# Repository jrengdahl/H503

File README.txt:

STM32H503RB test board and firmware

This project includes a small OSHPark board for the new H503
microcontroller from ST MIcro, and firmware to run on the board. The
firmware includes OpenMP support for this bare metal microcontroller.

THE CHIP

The STM32H503 is a low-end microcontroller by ST Microelectronics:
-- Cortex-M33 CPU
-- 250 MHz
-- 128K flash
-- 32K RAM
-- typical peripherals for a small micro, including USB Device.
-- ETM trace port

When this chip first became available in early March of 2023, it was in
stock at Mouser for $4.33, and I was able to obtain a few. As of March
2024 they are available in small quantities from Digikey, directly from
ST Micro, and some other suppliers. Try findchips.com to search for
availability. Often such chips are more easily available on a Nucleo
board (although the Nucleo boards do not have trace connectors).

The spec clock for the H503 is 250 Hz. It seems to run reliably up to
350 MHz, and sometimes 400 MHz, at room temperature, and not using all
the chip's features. YMMV.

THE FIRMWARE

The firmware build is managed by an STM32CubeIDE project. The skeleton
of the project was auto-generated from the H503.ioc file. My firmware is
a simple command line interpeter with the following commands:

-- dump memory
-- modify memory
-- fill memory
-- RAM test
-- input from a pin
-- output to a pin
-- calibrate the CPU clock (to make sure the crystal, PLL, and spin-delay loop are correct)
-- set the CPU clock to a given frequency
-- execute a single LDR to a given memory location
-- execute a single STR to a given memory location
-- print a summary of the flash and RAM
-- run a benchmark of the thread switcher
-- display the on-chip temperature sensor reading
-- dump the thread stacks
-- display the state of the free memory system
-- run various OpenMP tests
-- set the debug verbosity level
-- print the help

The command line processor is simple and easily expanded with new commands.

The firmware takes about 40K of flash and 24K of RAM.

For similar L412 and H743 projects, rather than using an FTDI
USB-to-serial cable, or an on-board USB-to-serial chip, I decided to
learn how to use the native on-chip USB for the serial console. I got a
lot of help from Jean Roch's tutorial on using the STM32 USB CDC
library:
https://nefastor.com/microcontrollers/stm32/usb/stm32cube-usb-device-library

When I went to port this firmware over to the H503 I found that, since
the chip is very new, the USB_Device library is not yet available. With
some help from ST tech support, I was able to borrow code from similar
chips (the H743 and L552), and adapt it to the H503.

THREADS

I usually write bare metal firmware, with no OS or RTOS, but I use a
simple non-preemptive threading system, which enables me to architect a
system as a set of cooperating processes. As the concept developed over
many years it has gone by the name of "wait-wake", "plastic fork", and
"not-an-OS", but currently goes by the name of "Bear Metal Threads". Its
characteristics include:

-- very small: the code that gets used at runtime consists of 23 ASM
   instructions. There is a little more for creating threads at powerup. 
-- very fast: a thread switch takes 125 nanoseconds on a 250 MHz M33.
-- non-preemptive: there is no scheduler.
-- threads can run at interrupt level, which can provide prioritization.

OPENMP

One reason I created this project is as a platform to experiment with
bare metal OpenMP. 

OpenMP is a parallel processing extension for C/C++ and Fortran that is
built into GCC. It can be used on modern multi-core PCs running Windows
and Linux. It is most commonly associated with massively parallel
supercomputers such as Frontier and Fugaku (https://www.top500.org). I
aim to show that it can also be useful for multi-threaded and parallel
programming on single and multi-core embedded processors.

The following OpenMP features are working:
-- parallel
-- parallel for
-- single
-- task
-- firstprivate

I have started migrating the powerup code and command line interpreter
to using OpenMP primitives rather than the older threading calls to
spawn new threads.

This is experimental and ongoing.

THE GCC TOOLCHAIN

There are two reasons this firmware requires a special toolchain:

-- The threading system reserves r9 for the preempted thread stack. The
entire firmware must be compiled with the GCC flag "-ffixed-r9", so that
user code does not clobber r9. According to the AAPCS specification, r9
should be untouched by libraries. I have never seen a precompiled ibrary
that observes this rule. Fortunately, the ST-supplied code is always
compiled along with your firmware. Unfortunately, the precompiled newlib
that comes with the standard ARM bare metal GCC toolchain does not
follow the rule and clobbers r9.

-- GCC includes OpenMP, however it is only enabled for platforms that
have a large OS, such as Linux or Windows. The bare metal versions of
the toolchain do not have OpenMP enabled. My build of the GCC bare metal
toolchain has OpenMP enabled.

The Cortex-M33 GCC 12.2 toolchain to be used with this project is found at:
https://github.com/jrengdahl/cross/releases

THE BOARD

The KiCAD project for the board is included, or you can order three
boards from OSHPark for $16.
https://oshpark.com/shared_projects/t9n5Q26a

The board uses the Arduino Nano form factor, but is only partially
pin-compatible. It will fit into a Nano socket, such as this:
https://www.amazon.com/gp/product/B095XVVGQ8. Since the H503 is only
available in a 64-pin LQFP at the moment, in order to fit it on the
board I had to turn it 45 degrees, and delete the middle three pins from
each row of the connector. On the other hand, all pins on the
microcontroller either have a job, are brought out to pins, or are
brought out to solderable test points.

Interesting things about the board are:
-- Arduino Nano form factor
-- can be powered from the USB port
-- uses the on-chip USB for a virtual serial console
-- trace port
-- SPI flash

Otherwise the board is very minimal: power regulator, crystal
oscillator, connectors, a reset button, the BOOT0 button is also an GPIO
input, and one LED. I put a Winbond SPI flash on it because I want to
learn how to use them.

The microcontroller pinout is captured in a CubeMX project,
H503.kicad/H503.ioc. This is a sample CubeMX project I used as reference
for the board design, which shows a possible maximum usage of the pins.
The separate ./H503.ioc used by the firmware project only enables the
pins that are currently supported by the firmware.

Building the board is not hard. I do my soldering under a 1959
StereoZoom microscope using a very fine-tip pencil, and SMT solder paste
applied with a toothpick, or wire solder for through-hole parts. One
thing to watch out for is the USB connector. If you use too little
solder you risk ripping the connector off the board if you are not real
careful with the USB cable. If you use too much solder it can puddle
under the connector and short out the signal pins.

There is a newer version of the board that was manufactured by JLCPCB.
All the small commodity parts are located on the bottom side and are
soldered by JLCPCB. The CPU, connectors, and a couple parts that are
not sourced by JLCPCB are on the top side and have to be hand soldered.

The directory H503-0.1.oshpark contains the KiCad files that were used
for the OSHPark board. The directory H503-0.2.jlcpcb contains the KiCad
files for the JLCPCB board. The "production" subdirectory contains the
zip file that was uploaded to JLCPCB, including the BOM and
pick-and-place files. The directory H503-0.3 contains a slight
modification to the H503-0.2 board layout; mainly, the oscillator
footprint uses larger pads to make it easier to solder by hand. (I have
not had the 0.3 board built yet).

TRACE

One of my retirement presents to myself was a Segger J-Trace probe, so
I put a 20-pin trace port on this board rather than the usual four-pin
Serial Wire Debug port. If you don't have a trace probe you can populate
a 10-pin connector instead, and use a J-link or ST-Link probe. (You
can't fit a 10-pin connector onto a 20 pin header because the end of the
connector won't fit between the 5th and 6th pairs of pins).

One reason I prefer the M7 processors is that they include an on-chip
trace buffer, and a trace probe is not required. I use the free Segger
Ozone debugger, which can display trace for either on-chip or off-chip
trace. Unfortunately, since COVID, M7 chips are nearly impossible for a
hobbyist to obtain. That is why I have been focusing on the L412, and
more recently the H503. (Try lcsc.com if you need M7 chips, I found some
affordable H7B0).

In order to use ETM trace with Cortex-M4 and Cortex-M33 chips, the
following is required:

-- a chip that has trace port or on-chip trace buffer. As far as I know,
all STM32 in 100 pin packages or larger have trace ports. Trace ports on
smaller pinouts are less common. There is no easy way to find which chips
have trace capability, other than reading many data sheets. So far I
have found the STM32H503 and STM32L412 in LQFP-64, and the L412 in
LQFP-32, have 5-pin trace ports. In fact, the L412 seems to be the only
STM32 in LQFP-32 that has a trace port.

Some Cortex-M7 chips from ST Micro have 2K or 4K on-chip trace buffers.
These can be used with Ozone and an inexpensive J-Link Edu, though the
trace depth is limited.

-- a trace probe (unless you have an on-chip trace buffer). Trace probes
are expensive. I am familiar with Lauterbach, which costs in the
vicinity of $10,000. My Segger J-Trace was around $1800. In the UK or EU
check out pdqlogic.com, but they won't ship to the USA. Some people have
used inexpensive USB logic analyzers with the Sigrok software to capture
trace, but such a solution is harder to use
(https://essentialscrap.com/tips/arm_trace).

-- a trace capable debugger. I use Segger Ozone, which is included 
with J-Trace, or it is free for non-commercial use.

-- you have to allocate from two to five pins for the trace port. I have
always used the full five pins.

-- Your board has to have a trace port connector. The traces from the
chip to the connector should be laid out with high speed signalling in
mind. In theory, it might be possible to wire a trace probe to I/O pins
of a Nucleo board, but I would not expect this to work well at fast
clock rates. Though the H503 can run up to 250 MHz (400 MHz overclocked),
on my board the trace becomes flakey above 100 MHz.

-- You need to configure the trace pins. There are two ways to do this:

     -- your software can setup the pins and the ETM at powerup.
        Currently my L412 software does it this way. I based my ETM
        setup code on this project:
        https://github.com/PetteriAimonen/STM32_Trace_Example

     -- You can obtain or write an Ozone script to setup the trace
        pins. Once the pins are setup, Ozone can deal with the ETM and
        TPIU on its own. Segger provides compiled (.pex) scripts for
        certain chips. If your chip is not supported, or you have used a
        different pinout than Segger used, you either have to get them
        to create a .pex for you, or you can write your own script. This
        project includes a redistributable .jdebug script which sets up
        the pins for the H503.

   Having tried both methods, using the script works a lot better. Note
   that the H503 uses a different ETM than the L412. The L412 code will
   not work for the H503. It would be fairly difficult to research and
   write the ETM-M33 setup code, since you not only have to deal with
   the pins, but also the ETM and TPIU, for which I could find no
   easy-to-use documentation or example code. Also, when using the
   script, the trace starts at powerup, whereas if your software sets up
   the ETM, the trace only works after your code runs, and you have to
   stop and restart your program after the setup code before Ozone
   starts receiving trace data.

RTOS-AWARE TRACE

Segger's Ozone debugger can detect RTOS thread switches in order to make
the trace easier to read and understand. If you are using a supported
RTOS they have RTOS-awareness modules you can download and use. If your
RTOS is not supported, or home-brewed like mine, you can tell Ozone
about the thread switching code in the Ozone startup script. The .jdebug
script included with this project does that. There are two prequisites:
your thread switch code must exist in a subroutine call that Ozone can
find, and you have to use Dwarf-4 debug info. Newer editions of GCC,
such as 12.2, emit Dwarf-5 debug data by default, so you have to pass
-gdwarf-4 to the GCC and G++ compilers.

The newer version of Ozone supports Dwarf-5, but I have not tried
Dwarf-5 yet.

JLINK

There is an alternate H503-edu.jdebug file that works with a non-trace
Jlink. The J-link Edu comes with a 10-pin high density conector that
will work with this board if you install a 10 pin connector (or cut half
the pins from the 20-pin connector). Jlink EDU is $60 at
https://shop-us.segger.com/product/j-link-edu-mini-8-08-91 or
at Mouser or Digikey.

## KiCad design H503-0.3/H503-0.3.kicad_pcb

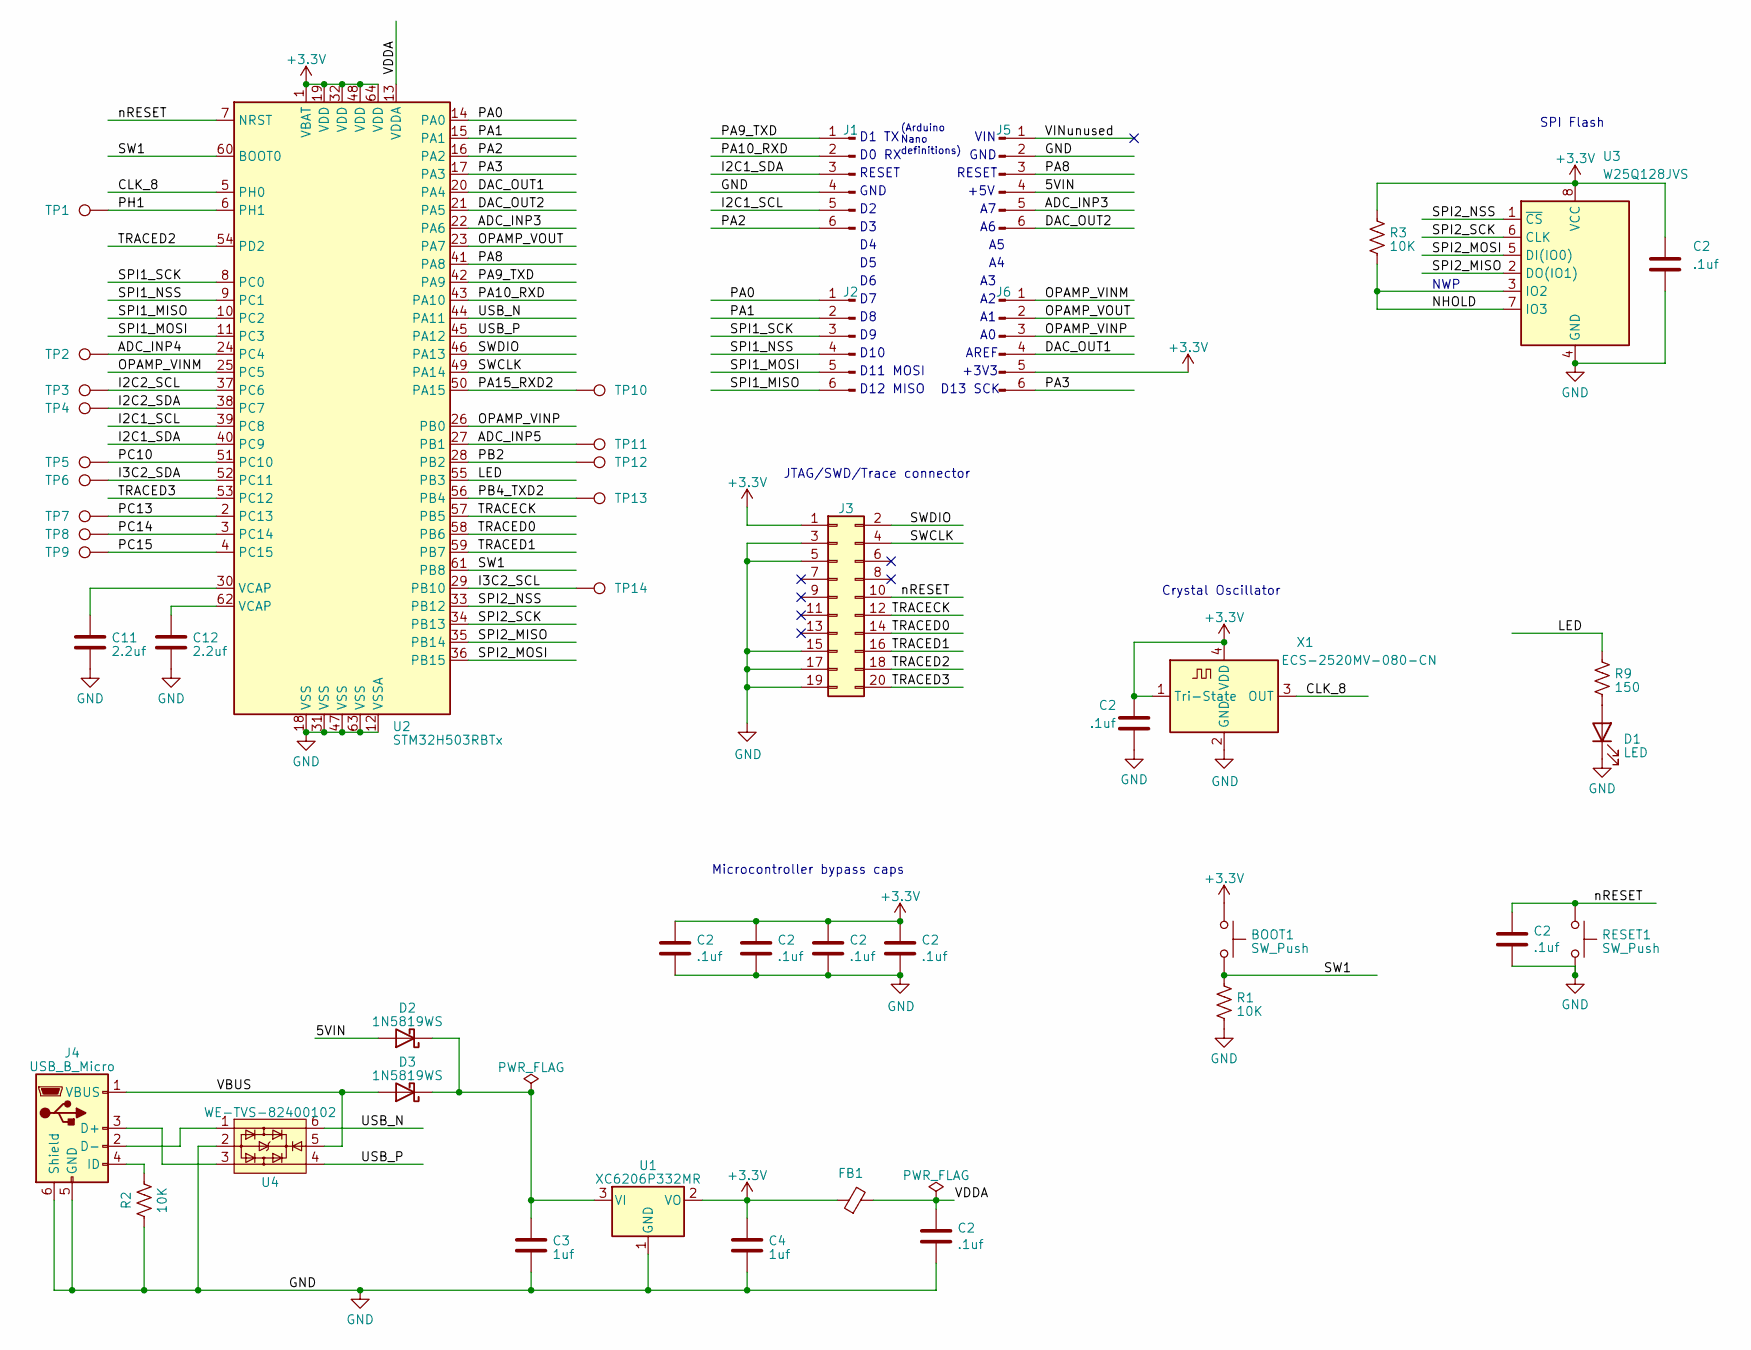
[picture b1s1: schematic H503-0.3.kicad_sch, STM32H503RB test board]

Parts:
BOOT1: SW_Push; SW_SPST_B3U-1000P
C2: .1uf; C_0603_1608Metric; LCSC C14663
C3, C4: 1uf; C_0805_2012Metric; LCSC C28323
C11, C12: 2.2uf; C_0805_2012Metric; LCSC C49217
D1: LED; LED_PLCC-2_3.4x3.0mm_KA
D2, D3: 1N5819WS; D_SOD-323; LCSC C191023
FB1: C_0603_1608Metric; LCSC C1002
J1, J2, J5, J6: Conn_01x06_Pin; PinHeader_1x06_P2.54mm_Vertical__min
J3: Conn_02x10_Odd_Even; PinHeader_2x10_P1.27mm_Vertical
J4: USB_B_Micro; USB_Micro-B_Amphenol_10118194_Horizontal
R1, R2, R3: 10K; R_0603_1608Metric; LCSC C25804
R9: 150; R_0603_1608Metric; LCSC C22808
RESET1: SW_Push; SW_SPST_B3U-1000P
TP1, TP2, TP3, TP4, TP5, TP6, TP7, TP8, TP9, TP10, TP11, TP12, TP13, TP14: TestPoint; TestPoint_THTPad_D1.0mm_Drill0.5mm_min
U1: XC6206P332MR; SOT-23-3; LCSC C5446
U2: STM32H503RBTx; LQFP-64_10x10mm_P0.5mm
U3: W25Q128JVS; SOIC-8_5.23x5.23mm_P1.27mm
U4: WE-TVS-82400102; SOT-23-6
X1: ECS-2520MV-080-CN; Oscillator_SMD_ECS_2520MV-4Pin_2.5x2.0mm-hand-solder

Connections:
/5VIN: D2.2 (A), J5.4
/ADC_INP3: J5.5, U2.22 (PA6)
/ADC_INP4: TP2.1, U2.24 (PC4)
/ADC_INP5: TP11.1, U2.27 (PB1)
/CLK_8: U2.5 (PH0), X1.3 (OUT)
/DAC_OUT1: J6.4, U2.20 (PA4)
/DAC_OUT2: J5.6, U2.21 (PA5)
/I2C1_SCL: J1.5, U2.39 (PC8)
/I2C1_SDA: J1.3, U2.40 (PC9)
/I2C2_SCL: TP3.1, U2.37 (PC6)
/I2C2_SDA: TP4.1, U2.38 (PC7)
/I3C2_SCL: TP14.1, U2.29 (PB10)
/I3C2_SDA: TP6.1, U2.52 (PC11)
/LED: R9.2, U2.55 (PB3)
/NHOLD: R3.2, U3.3 (IO2), U3.7 (IO3)
/OPAMP_VINM: J6.1, U2.25 (PC5)
/OPAMP_VINP: J6.3, U2.26 (PB0)
/OPAMP_VOUT: J6.2, U2.23 (PA7)
/PA0: J2.1, U2.14 (PA0)
/PA1: J2.2, U2.15 (PA1)
/PA2: J1.6, U2.16 (PA2)
/PA3: J6.6, U2.17 (PA3)
/PA8: J5.3, U2.41 (PA8)
/PA9_TXD: J1.1, U2.42 (PA9)
/PA10_RXD: J1.2, U2.43 (PA10)
/PA15_RXD2: TP10.1, U2.50 (PA15)
/PB2: TP12.1, U2.28 (PB2)
/PB4_TXD2: TP13.1, U2.56 (PB4)
/PC10: TP5.1, U2.51 (PC10)
/PC13: TP7.1, U2.2 (PC13)
/PC14: TP8.1, U2.3 (PC14)
/PC15: TP9.1, U2.4 (PC15)
/PH1: TP1.1, U2.6 (PH1)
/SPI1_MISO: J2.6, U2.10 (PC2)
/SPI1_MOSI: J2.5, U2.11 (PC3)
/SPI1_NSS: J2.4, U2.9 (PC1)
/SPI1_SCK: J2.3, U2.8 (PC0)
/SPI2_MISO: U2.35 (PB14), U3.2 (DO(IO1))
/SPI2_MOSI: U2.36 (PB15), U3.5 (DI(IO0))
/SPI2_NSS: U2.33 (PB12), U3.1 (~CS)
/SPI2_SCK: U2.34 (PB13), U3.6 (CLK)
/SW1: BOOT1.2, R1.1, U2.60 (BOOT0), U2.61 (PB8)
/SWCLK: J3.4, U2.49 (PA14)
/SWDIO: J3.2, U2.46 (PA13)
/TRACECK: J3.12, U2.57 (PB5)
/TRACED0: J3.14, U2.58 (PB6)
/TRACED1: J3.16, U2.59 (PB7)
/TRACED2: J3.18, U2.54 (PD2)
/TRACED3: J3.20, U2.53 (PC12)
/USB_N: U2.44 (PA11), U4.6
/USB_P: U2.45 (PA12), U4.4
/VBUS: D3.2 (A), J4.1 (VBUS), U4.5
/VINunused: J5.1
GND: C2.2, C3.2, C4.2, C11.2, C12.2, D1.1 (K), J1.4, J3.3, J3.5, J3.15, J3.17, J3.19, J4.5 (GND), J4.6 (Shield), J5.2, R1.2, R2.1, RESET1.2, U1.1 (GND), U2.12 (VSSA), U2.18 (VSS), U2.31 (VSS), U2.47 (VSS), U2.63 (VSS), U3.4 (GND), U4.2, X1.2 (GND); also elsewhere on the board
unnamed: C3.1, D2.1 (K), D3.1 (K), U1.3 (VI)
unnamed: C11.1, U2.30 (VCAP)
unnamed: C12.1, U2.62 (VCAP)
unnamed: D1.2 (A), R9.1
unnamed: J4.3 (D+), U4.3
unnamed: J4.2 (D-), U4.1
unnamed: J4.4 (ID), R2.2

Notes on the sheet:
+3V3
SPI Flash
VIN
NWP
+5V
GND
Microcontroller bypass caps
D13 SCK
D12 MISO
Crystal Oscillator
D1 TX
RESET
JTAG/SWD/Trace connector
D11 MOSI
D0 RX
(Arduino Nano definitions)
AREF
D10

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
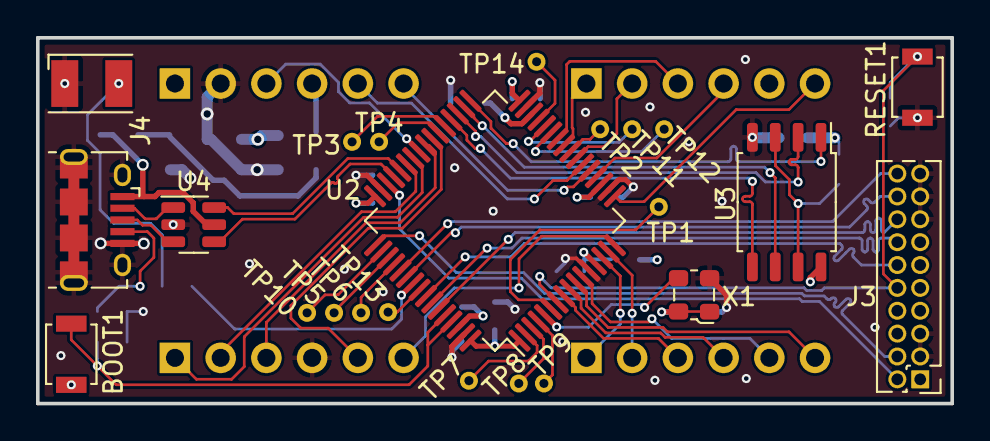
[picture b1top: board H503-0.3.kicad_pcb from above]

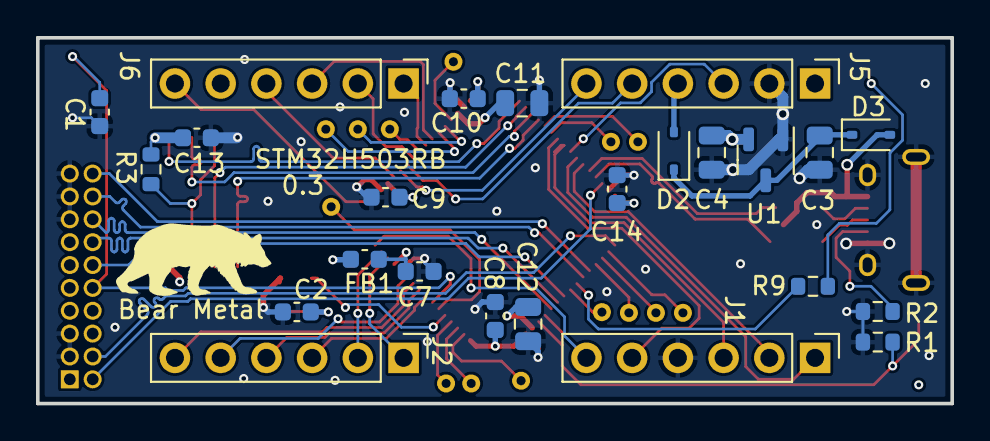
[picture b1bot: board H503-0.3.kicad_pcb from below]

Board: 4 copper layers, 50.8 x 20.3 mm, 47 parts (24 on the bottom side), 63 nets.

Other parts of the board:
C1, C7, C8, C9, C10, C13, C14: .1uf; C_0603_1608Metric

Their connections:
GND: C1.2, C7.2, C8.2, C9.2, C10.2, C13.2, C14.2; also elsewhere on the board

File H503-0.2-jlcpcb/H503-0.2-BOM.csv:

"Id";"Designator";"Footprint";"Quantity";"Designation";"Supplier and ref";
1;"X1";"Oscillator_SMD_ECS_2520MV-xxx-xx-4Pin_2.5x2.0mm";1;"ECS-2520MV-080-CN";;;
2;"TP1,TP3,TP7,TP14,TP9,TP6,TP11,TP5,TP8,TP12,TP4,TP13,TP2,TP10";"TestPoint_THTPad_D1.0mm_Drill0.5mm_min";14;"TestPoint";;;
3;"BOOT1,RESET1";"SW_SPST_B3U-1000P";2;"SW_Push";;;
4;"J3";"PinHeader_2x10_P1.27mm_Vertical";1;"Conn_02x10_Odd_Even";;;
5;"U4";"SOT-23-6";1;"WE-TVS-82400102";;;
6;"J4";"USB_Micro-B_Amphenol_10118194_Horizontal";1;"USB_B_Micro";;;
7;"U2";"LQFP-64_10x10mm_P0.5mm";1;"STM32H503RBTx";;;
8;"U3";"SOIC-8_5.23x5.23mm_P1.27mm";1;"W25Q128JVS";;;
9;"D1";"LED_PLCC-2_3.4x3.0mm_KA";1;"LED";;;
10;"C10,C14,C1,C9,C8,C7,C2,C13";"C_0603_1608Metric";8;".1uf";;;
11;"U1";"SOT-23-3";1;"XC6206P332MR";;;
12;"R1,R2,R3";"R_0603_1608Metric";3;"10K";;;
13;"J1,J2,J6,J5";"PinHeader_1x06_P2.54mm_Vertical__min";4;"Conn_01x06_Pin";;;
14;"FB1";"C_0603_1608Metric";1;"~";;;
15;"D2,D3";"D_SOD-323";2;"1N5819WS";;;
16;"C11,C12";"C_0805_2012Metric";2;"2.2uf";;;
17;"R9";"R_0603_1608Metric";1;"150";;;
18;"C3,C4";"C_0805_2012Metric";2;"1uf";;;

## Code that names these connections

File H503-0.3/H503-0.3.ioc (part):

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Mcu.Name=STM32H503RBTx
Mcu.Package=LQFP64
Mcu.UserName=STM32H503RBTx
PA0.Mode=NSS_Signal_Hard_Output
PA0.Signal=SPI3_NSS
PA1.Mode=Full_Duplex_Master
PA1.Signal=SPI3_SCK
PA10.Mode=Asynchronous
PA10.Signal=USART1_RX
PA11.Mode=Device
PA11.Signal=USB_DM
PA12.Mode=Device
PA12.Signal=USB_DP
PA13(JTMS/SWDIO).GPIOParameters=GPIO_Label
PA13(JTMS/SWDIO).GPIO_Label=SWDIO
PA13(JTMS/SWDIO).Mode=Trace_Synchro_4bits_SW
PA13(JTMS/SWDIO).Signal=DEBUG_JTMS-SWDIO
PA14(JTCK/SWCLK).GPIOParameters=GPIO_Label
PA14(JTCK/SWCLK).GPIO_Label=SWCLK
PA14(JTCK/SWCLK).Mode=Trace_Synchro_4bits_SW
PA14(JTCK/SWCLK).Signal=DEBUG_JTCK-SWCLK
PA15(JTDI).Mode=Asynchronous
PA15(JTDI).Signal=USART2_RX
PA2.Mode=Full_Duplex_Master
PA2.Signal=SPI3_MISO
PA3.Mode=Full_Duplex_Master
PA3.Signal=SPI3_MOSI
PA4.Signal=COMP_DAC11_group
PA5.Signal=COMP_DAC12_group
PA6.Signal=ADCx_INP3
PA7.Signal=SharedAnalog_PA7
PA8.GPIOParameters=GPIO_Label
PA8.GPIO_Label=PA8
PA8.Signal=GPIO_Input
PA9.Mode=Asynchronous
PA9.Signal=USART1_TX
PB0.Mode=Standalone
PB0.Signal=OPAMP1_VINP
PB1.Signal=ADCx_INP5
PB10.Mode=Controller
PB10.Signal=I3C2_SCL
PB12.Mode=NSS_Signal_Hard_Output
PB12.Signal=SPI2_NSS
PB13.Mode=Full_Duplex_Master
PB13.Signal=SPI2_SCK
PB14.Mode=Full_Duplex_Master
PB14.Signal=SPI2_MISO
PB15.Mode=Full_Duplex_Master
PB15.Signal=SPI2_MOSI
PB2.GPIOParameters=GPIO_Label
PB2.GPIO_Label=PB2
PB2.Signal=GPIO_Input
PB3(JTDO/TRACESWO).GPIOParameters=GPIO_Label
PB3(JTDO/TRACESWO).GPIO_Label=LED
PB3(JTDO/TRACESWO).Signal=GPIO_Output
PB4(NJTRST).Mode=Asynchronous
PB4(NJTRST).Signal=USART2_TX
PB5.GPIOParameters=GPIO_Label
PB5.GPIO_Label=TRACECK
PB5.Mode=Trace_Synchro_4bits_SW
PB5.Signal=DEBUG_TRACECLK
PB6.GPIOParameters=GPIO_Label
PB6.GPIO_Label=TRACED0
PB6.Mode=Trace_Synchro_4bits_SW
PB6.Signal=DEBUG_TRACED0
PB7.GPIOParameters=GPIO_Label
PB7.GPIO_Label=TRACED1
PB7.Mode=Trace_Synchro_4bits_SW
PB7.Signal=DEBUG_TRACED1
PB8.GPIOParameters=GPIO_Label
PB8.GPIO_Label=SW1
PB8.Signal=GPIO_Input
PC0.Mode=Full_Duplex_Master
PC0.Signal=SPI1_SCK
PC1.Mode=NSS_Signal_Hard_Output
PC1.Signal=SPI1_NSS
PC10.GPIOParameters=GPIO_Label
PC10.GPIO_Label=PC10
PC10.Signal=GPIO_Input
PC11.Mode=Controller
PC11.Signal=I3C2_SDA
PC12.GPIOParameters=GPIO_Label
PC12.GPIO_Label=TRACED3
PC12.Mode=Trace_Synchro_4bits_SW
PC12.Signal=DEBUG_TRACED3
PC13.GPIOParameters=GPIO_Label
PC13.GPIO_Label=PC13
PC13.Signal=GPIO_Input
PC14-OSC32_IN(OSC32_IN).GPIOParameters=GPIO_Label
PC14-OSC32_IN(OSC32_IN).GPIO_Label=PC14
PC14-OSC32_IN(OSC32_IN).Signal=GPIO_Input
PC15-OSC32_OUT(OSC32_OUT).GPIOParameters=GPIO_Label
PC15-OSC32_OUT(OSC32_OUT).GPIO_Label=PC15
PC15-OSC32_OUT(OSC32_OUT).Signal=GPIO_Input
PC2.Mode=Full_Duplex_Master
PC2.Signal=SPI1_MISO
PC3.Mode=Full_Duplex_Master
PC3.Signal=SPI1_MOSI
PC4.Signal=ADCx_INP4
PC5.Mode=Standalone
PC5.Signal=OPAMP1_VINM
PC6.Mode=I2C
PC6.Signal=I2C2_SCL
PC7.Mode=I2C
PC7.Signal=I2C2_SDA
PC8.Mode=I2C
PC8.Signal=I2C1_SCL
PC9.Mode=I2C
PC9.Signal=I2C1_SDA
PD2.GPIOParameters=GPIO_Label
PD2.GPIO_Label=TRACED2
PD2.Mode=Trace_Synchro_4bits_SW
PD2.Signal=DEBUG_TRACED2
PH0-OSC_IN(PH0).Mode=HSE-External-Clock-Source
PH0-OSC_IN(PH0).Signal=RCC_OSC_IN
PH1-OSC_OUT(PH1).GPIOParameters=GPIO_Label
PH1-OSC_OUT(PH1).GPIO_Label=PH1
PH1-OSC_OUT(PH1).Signal=GPIO_Input
RCC.HSE_VALUE=8000000
RCC.SYSCLKFreq_VALUE=250000000
RCC.SYSCLKSource=RCC_SYSCLKSOURCE_PLLCLK
board=custom

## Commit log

2023-04-27 Initial project creation
2023-04-27 add USB Middlewares from H743 and USB_Device from L552
2023-04-27 Changes to get USB CDC to work.
    with a simple echo as the app.
2023-04-27 add my test software and get it working with USB console
2023-04-27 add KiCad project for the H503 board
2023-04-28 update schematic and create BOM
2023-04-28 worked on README.txt
    Added suspend/resume benchmark.
2023-04-28 work on documentation
2023-04-29 more comments
2023-04-29 optimize inline assembly for suspend and resume in thread.cpp
    Achieved nearly 8% improvement.
2023-04-29 One more optimization for thread.cpp.
    Now nearly 10% improvement.
    A thead switch now costs about 125 ns.
2023-04-30 add time/switch to thread benchmark test
    mods to README
2023-05-02 got trace working
    Delete trace pins from my project -- let the debugger manage them.
    Drop speed from 250 to 50 MHz to get trace to work. Will later bump it back up as much as possible and still have trace work.
2023-05-03 move imported USB stuff under Core/Src so the gode generator can't keep deleting it.
    set clock to 150 MHz
2023-05-03 move imported USB stuff under Core/Src so the code generator can't keep deleting it.
    set clock to 150 MHz
2023-05-03 change clock to 100 MHz
    trace seems to trip once in a while at 150
2023-05-05 add and use redistributable version of trace pin setup JScript
2023-05-05 fix .gitignore and add Drivers to the git project
    so the project is complete and can be compiled without
    re-generating the auto source code
2023-05-05 change PLL setup to make it easier to change CPU frequency on the fly
    try to fix __NOINLINE in STM32H5xx_hal_def.h
2023-05-05 make CPU frequency settable, step 1
    try again to fix __NOINLINE
2023-05-05 trying to make CPU clk variable, first try failed
    changed cyccnt.hpp
    added clk command to interp
2023-05-05 variable CPU clock command works!
    Added SystemClock_HSI_Config and SystemClock_PLL_Config in main.c
    You have to select another clock besides the PLL before reprogramming it,
    the SystemClock_Config function does not do that automatically.
    Tested at 50, 100, 150, 200, and 250.
2023-05-05 add warning about trace if clock is over 100 MHz
2023-05-07 snapshot, working on changes to thread switches to make them comprehensible to RTOS-aware tracing
    code works, but trace timeline still doesn't have it exactly right
2023-05-08 got RTOS-awareness working for Bear Metal Threads
    The key is refactoring the switch routines, and
    passing -gdwarf-4 to the compiler.
2023-05-08 optimize thread switching for RTOS awareness
2023-05-09 start adding libgomp
    plus some dcumentation/comments additions and cleanup
2023-05-24 add tmp (temperature) command
    refactor thread to context
2023-05-24 add omp test
    add verbose command
    change USB serial so only one thread switch is required per newline
    align omp thread stacks for debugging
2023-05-31 rewrote context switching for OMP
    (worked on the second try)
2023-06-02 add "stk" command to dump stacks
    add "id" to omp_thread
    fix omp_get_thread_num
    add operator bool to Port
    adjust stacks and number of OMP threads and tasks to conserve memory on
    make background use the "user stack" rather than the end of memory
    implement mutex.h for H503
2023-06-14 add H503-edu.jdebug
2023-06-23 partial rewrite of libgomp, moving toward using OpenMP as RTOS
    more implementation of teams
    add fast, simple malloc
    add arg to spawn
    It works! On the first try!
    Improved stk command.
    Added arg to omp 0 test (number of threads).
2023-06-23 add test for parallel for
2023-06-27 add "single" test
    single does not work, need to add code so interp is a OMP thread
    rewrite GOMP_barrier
2023-07-19 working on getting "permute" to work
    explicit tasks somewhat working at this point
2023-07-27 got permute to work
    renamed ThreadFIFO to ContextFIFO
    fixed ASM for ContextFIFO
    add name string to omp_thread for debug
    make background and inter OMP threads
    mutex.h uses ContxtFIFO instead of Port
    improved "stk" command
2023-07-28 start interp using OMP directives
    the background polling loop is now embedded inside GOMP_parallel
2023-07-28 found a better way to run background and interp
    moved background polling loop back to background.cpp, using
    a team of two threads to run background loop (0) and interp (1)
2023-07-29 fix background's team pointer (0xffffffff)
    comments
2023-07-29 improve debug reporting of thread IDs
2023-08-01 add LinkedList.hpp
2023-08-01 added member pointer to next in LinkedList.hpp
2023-08-02 added task_list to team; remove global ready_tasks
    use LinkedList for members and task_list
    permute appears to work now
2023-08-02 fix team pointer in gomp_worker
2023-08-04 fix memory leak in malloc
    add "mem" command to display free memory pool state
2024-01-05 Add libgomp_reinit to reset default number of threads after an OpenMP program has terminated.
    Add op_get_wtime and omp_get_wtick, but they are based on the 32-bit cycle counter which is only good for 42 seconds at 100 MHz, or
    17 seconds at 250 MHz. I need to fire up one of the 64 bit timers.
2024-01-05 Add libgomp_reinit to reset default number of threads after an OpenMP program has terminated.
    Add op_get_wtime and omp_get_wtick, but they are based on the 32-bit cycle counter which is only good for 42 seconds at 100 MHz, or
    17 seconds at 250 MHz. I need to fire up one of the 64 bit timers.
    (Forgot to stage the changes on the last commit).
2024-01-05 Migrate project to new version of STM32CubeIDE.
    This updates a lot of drivers and also sometimes causes code generation to change.
    Changed cmsis.h so that the definition of __NOINLINE matches the HAL version, to suppress redefinition warning.
    Also had to change one CubeMX clock tree setting to get rid of a new error message.
2024-01-05 Print build date/time stamp at startup.
2024-01-06 Rewrote omp_get_wtime to use TIM2, which is clocked at 1 MHz.
    Enabled and setup TIM2.
    Added test of omp_get_wtime to the calibrate command.
2024-01-06 Update TIM2 prescaler when clock frequency is changed so that TIM2 always counts microseconds.
    Daisy-chain omp.h with a local version to add customized definitions.
    Add single-precision floating point versions of omp_get_wtime and omp_get_wtick.
2024-01-09 Add float omp_get_wtime(int) and float omp_get_wtick(int)
    Comments.
2024-01-09 Rewrite threading benchmark; remove TestStack; (not working yet).
    context.hpp: added function to return the current Context pointer (r9).
    interp.cpp: add help for omp tests.
2024-01-10 Optimized OpenMP thread scheduler; rather than a yield in a spin loo, the non-busy threads now suspend. Background polls and resumes them when needed.
    Added call to gomp_poll_threads in background loop.
2024-01-10 Optimize thread switching.
    Got the thread switching benchmark to work again.
2024-01-11 optimize thread polling
2024-03-20 Add KiCad files for the JLCPCB board.
    The JLCPCB board comes with the parts on the bottom size presoldered.
    All you have to do is solder the top side and connectors.
    Updated README.
    Comments and minor firmware fine-tuning.
2024-05-15 Add a top-level makefile to create the missing .cyclo files
    This is to get rid of the warning about a pattern rule not making all
    its targets. This occurs because I use a custom GCC that does not
    support the -fcyclomatic-complexity option. You can turn the option off
    in the STM32 IDE's compiler settings, but the autogenerated Makefiles
    still contain .cyclo targets.
    Reorganize the directories under Core/Src.
2024-12-14 Copy updates from later work on the MSCP project, such as the temperature monitor.
    Update autogenerated libraries.
2024-12-19 Restructure interp. All commands are now in separate files.
    So the implementation of the foo command will now be found in
    FooCommand.cpp.
2024-12-19 Enable SPI2 for NOR flash
    This necessitated updating to the latest version of STM32CubeMX
    and its libraries.
    Reorganize stacks a bit, reduced sise of background and temperature
    monitor stacks, to gain space for FATFS later.
2024-12-20 Add FATFS and related files from the MSCP project This is a non-working snapshot.
2024-12-20 Snapshot of more WIP; first compile without error, but not tested at all.
2024-12-20 Snapshot. Moved USB_Device and USB_Device_Library to match MSCP project.
2024-12-20 snap
2024-12-21 Correct the sector and block sizes.
    This snapshot has a semi-working FATFS. A FATFS image can be downloaded
    to the NOR flash via Xmodem.
    Add "disk activity LED".
    Erase chip does NOT work.
2024-12-24 Improvements and instrumentation of Xmodem command; enable long file names in FATFS.
    Files names up to 64 characters, ASCII character set only.
2024-12-27 sync MSCP and H503
2024-12-27 add code to invers dsata read/written to SPI NOR
    Not fully tested yet.
2025-01-25 snapshot: added code for SD card support for FATFS
    not working yet
2025-01-26 Got FATFS working with an SD card
    connected via SPI1.
    Added multiple outputs to trigon/trigoff, added trigpulse.
